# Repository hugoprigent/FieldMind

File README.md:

**Français** · [English](README.en.md)

# FieldMind

**Un rover de terrain dont les missions et la perception sont pilotées par une IA locale.**

<p align="center"><em>Le rover, sans coque, avec la remorque porte-drone et le drone posé dessus.</em></p>

Projet de Hugo Prigent, finaliste du **ASUS Ascent GX10 AI Developer Challenge 2026**.
FieldMind relie un rover Raspberry Pi / ESP32, un poste opérateur web et des modèles exécutés sur un ASUS Ascent GX10. La navigation, les vérifications des commandes et l'arrêt restent dans le logiciel du rover.

L'objectif : aider un opérateur à explorer et documenter une zone difficile d'accès, puis partager les observations entre robots. Le prototype vise un fonctionnement de terrain sans API d'IA externe ; cette autonomie de déploiement reste à valider.

[**Simulation publique du poste**](https://hugoprigent.com/fieldmind/) · [Page projet](https://hugoprigent.com/projets/fieldmind) · [Pitch de candidature](https://youtu.be/ZIIjRc_pI_E) · [Architecture](docs/architecture.md) · [État au 23 octobre](docs/status-2026-10-23.md) · [Validation](docs/validation.md)

> **État au 23 octobre 2026.**
> - Le rover roule, avec son châssis et son électronique visibles ; la coque n'est pas montée. Il tourne par le différentiel des roues arrière depuis la panne du servo de direction.
> - Navigation autonome testée en intérieur le 21 octobre avec le GX10 : exploration sur la consigne « explore la pièce » et trajet autonome aller-retour sur la carte lidar.
> - La remorque porte-drone est fabriquée ; ses volets sont commandés par servos (firmware ESP32-C5 ROVER_4). Le tractage autonome n'est pas validé.
> - Drone : flux vidéo reçu sur le Pi ; niveau de batterie pas encore lu de façon fiable ; le vol autonome n’est pas validé.
> - Huit modèles servis sur le GX10 : Qwen3.6-35B-A3B NVFP4, RoboBrain 2.5, D-FINE, Depth Anything V2, SAM 2.1, Qwen3-ASR, Qwen3-TTS, Qwen3-VL-Embedding.

*Vue CAO du rover avec sa coque et la remorque. Le rover réel roule pour l'instant sans la coque.*

## Le prototype

| | |
| :---: | :---: |
|  |  |
| Essai de navigation dans un couloir, avec les caméras stéréo et le lidar sur le châssis. | Câblage de la planche : Raspberry Pi, contrôleurs moteurs, convertisseurs, batterie. |
|  | |
| Carte capteurs I²C : IMU et écran OLED qui affiche l'état des capteurs. | |

## Le poste de pilotage

*Pilotage (simulation publique) : caméra gauche avec le couloir projeté devant le rover, vue 3D en incrustation, lidar et modes à droite.*

*Carte (essai réel du 21 octobre) : carte d'occupation lidar, trajet parcouru et chemin prévu en mode auto.*

*Vue 3D (essai réel du 21 octobre) : murs issus du lidar, objets nommés par la vision du GX10, caméra du rover en incrustation.*

## Essayer le logiciel actuel, sans matériel

Python **3.13+** et [uv](https://docs.astral.sh/uv/) :

```bash
git clone https://github.com/hugoprigent/FieldMind.git
cd FieldMind/software/rover
uv venv --python 3.13 .venv
uv pip install --python .venv/bin/python -r requirements-ci.txt
FIELDMIND_IA_PROFIL=aucun .venv/bin/python -m fieldmind \
  --materiel simulation --scenario jardin --hote 127.0.0.1
```

Ouvrir **http://127.0.0.1:8080/**. Le matériel est simulé ; navigation, missions, sécurité et interface sont le code du rover. Ce démarrage ne demande aucune clé d'API et ne commande aucun matériel réel.

La [simulation publique](https://hugoprigent.com/fieldmind/) sert ce même poste web : chaque navigateur reçoit son propre rover simulé, sans accès au matériel. Son serveur est [`software/rover/fieldmind/public_demo.py`](software/rover/fieldmind/public_demo.py) ; il se lance localement avec `.venv/bin/python -m fieldmind.public_demo --hote 127.0.0.1 --port 8085`. Son déploiement et ses clés ne sont pas dans ce dépôt. La [première démo MuJoCo](software/README.md) reste disponible.

## Comment ça fonctionne

```mermaid
flowchart LR
    O[Opérateur : carte, texte, voix] --> P[Poste web]
    P --> R[Raspberry Pi : missions, carte, navigation]
    R <--> G[GX10 : modèles locaux, images et outils]
    R --> S[Validation et superviseur de sécurité]
    L[Lidar, caméras, IMU, GNSS] --> R
    L --> S
    S --> E[ESP32-C5 : commandes, capteurs, watchdog]
    E --> M[Traction et direction]
```

- **Rover** : lidar C1, stéréo, odométrie, carte d'occupation, navigation et journal des essais.
- **IA et missions** : consignes écrites ou dites, exploration progressive, mémoire spatiale, confirmation d'un objet sur plusieurs images. Le GX10 choisit parmi des points calculés par le Pi ; le Pi revalide le choix, navigue et garde la sécurité. Le modèle ne commande pas directement les moteurs.
- **GX10** : agent et vision (Qwen3.6-35B-A3B NVFP4), pointage (RoboBrain 2.5), détection (D-FINE), profondeur (Depth Anything V2), segmentation (SAM 2.1), parole (Qwen3-ASR, Qwen3-TTS), empreintes d'images (Qwen3-VL-Embedding). Une analyse de scène a pris environ 6 à 9 s pendant les essais réels. [Configuration](software/rover/deploiement/gx10/README.md) et [état par rôle](software/rover/MODELES.md).
- **Électronique** : firmware XIAO ESP32-C5, chien de garde, écran OLED, capteurs I²C et liaison USB avec le Pi. La version ROVER_4 commande les deux servos des volets de la remorque.
- **Mécanique** : pneus TPU, châssis en bois, direction actuelle par différentiel des roues arrière ; remorque porte-drone imprimée et assemblée. La coque est dessinée mais pas montée ; un support de servo SG90 pour la direction est dessiné, pas validé sous charge.

Pendant la session ASUS, le GX10 était distant et joint par réseau privé. Les modèles tournent localement sur le GX10, mais un déploiement complet hors réseau, sur le terrain, n'est pas encore démontré.

## Explorer le dépôt

| Dossier | Contenu |
| --- | --- |
| [`software/rover/`](software/rover/README.md) | Logiciel actuel du Pi, simulateur du matériel, poste web et simulation publique isolée, tests, pont ROS 2 |
| [`software/esp32/esp_c5/`](software/esp32/esp_c5/README.md) | Firmware PlatformIO et programmes de banc |
| [`software/rover/deploiement/gx10/`](software/rover/deploiement/gx10/README.md) | Configuration des services IA et vérificateur d'API |
| [`software/`](software/README.md) | Première simulation MuJoCo (antérieure au rover actuel) |
| [`cao/`](cao/README.md) | Pièces STL courantes, scripts Fusion et plans de fabrication |
| [`hardware/`](hardware/README.md) | Connexions actuelles et études électroniques KiCad |
| [`docs/status-2026-10-23.md`](docs/status-2026-10-23.md) | État du rover, de la remorque, du drone et du GX10 au 23 octobre |
| [`docs/validation.md`](docs/validation.md) | Ce qui est mesuré, ce qui est simulé, ce qui reste à vérifier |

## Vérifier

Depuis `software/rover`, avec l'environnement créé ci-dessus :

```bash
.venv/bin/python -m pytest -q -m "not lent"
node --test tests/web/*.test.mjs
```

Les tests couvrent les contrôleurs, la sécurité, la navigation, les contrats IA et les scénarios simulés. Ils ne remplacent pas les essais physiques. [Détails et limites](docs/validation.md).

## Matériel et droits

Avant un essai réel, lire le [guide rover](software/rover/README.md) et les [connexions](hardware/electronics/CONNEXIONS.md), calibrer le montage et prévoir une coupure de traction. Les documents KiCad comportent des études antérieures à certains branchements actuels : leur statut est indiqué dans [hardware/README.md](hardware/README.md).

Cette édition sélectionne les sources utiles à la démonstration, sans les fichiers d'accès, secrets, journaux privés, rushes ni historique de travail. [Provenance](docs/publication.md).

Le code et les conceptions originaux sont présentés pour consultation ; aucune licence libre globale n'est accordée à ce stade. Les composants tiers conservent leurs licences. Voir [droits](RIGHTS.md) et [crédits](THIRD_PARTY_NOTICES.md).

## Langues et vidéos

Le poste et la page projet sont disponibles en français et en anglais : sélecteur **FR / EN** en haut à droite, détection de la langue du navigateur et choix mémorisé.

- [Présentation et essais en français](https://hugoprigent.com/media/fieldmind/presentation-20261023c.mp4)
- [Presentation and tests in English](https://hugoprigent.com/media/fieldmind/presentation-20261023-en.mp4)
- [Page projet en français](https://hugoprigent.com/projets/fieldmind?lang=fr) · [Project page in English](https://hugoprigent.com/projets/fieldmind?lang=en)

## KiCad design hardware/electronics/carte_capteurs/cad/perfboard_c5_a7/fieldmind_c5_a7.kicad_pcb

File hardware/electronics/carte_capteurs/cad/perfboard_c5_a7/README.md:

**Français** · [English](README.en.md)

# Projet courant A7 — une perfboard 4 × 6 cm, tous les fils dessous

Ouvrir `fieldmind_c5_a7.kicad_pro` dans KiCad 10. Toutes les sources ont été enregistrées par KiCad 10.0.6.

- **Schéma** : une feuille racine (XIAO, GNSS J4, extensions J6 et J8, Modulino Knob J7) et une sous-feuille, « Capteurs I2C et écran ».
- **PCB** :
  - **F.Cu** : uniquement les ponts de soudure du XIAO, côté écran ;
  - **B.Cu** : fils nus de la face dessous ;
  - **In1.Cu / In2.Cu** : fils isolés de la face dessous. Ce ne sont pas des couches réelles : elles séparent les fils qui se croisent pour le DRC ;
  - `PL1` porte les 280 trous ; `Cmts.User` porte les numéros de fils ;
  - la vue 3D s'ouvre avec Alt+3.
- Ne pas faire « Mettre à jour le PCB depuis le schéma » sans précaution : les pastilles de `PL1` portent leurs nets à la main.

Documentation : `../../perfboard_une_plaque_c5_a7.md`. Régénération : `scripts/generer_c5_a7.py --force`, ce qui **écrase toute édition manuelle**.

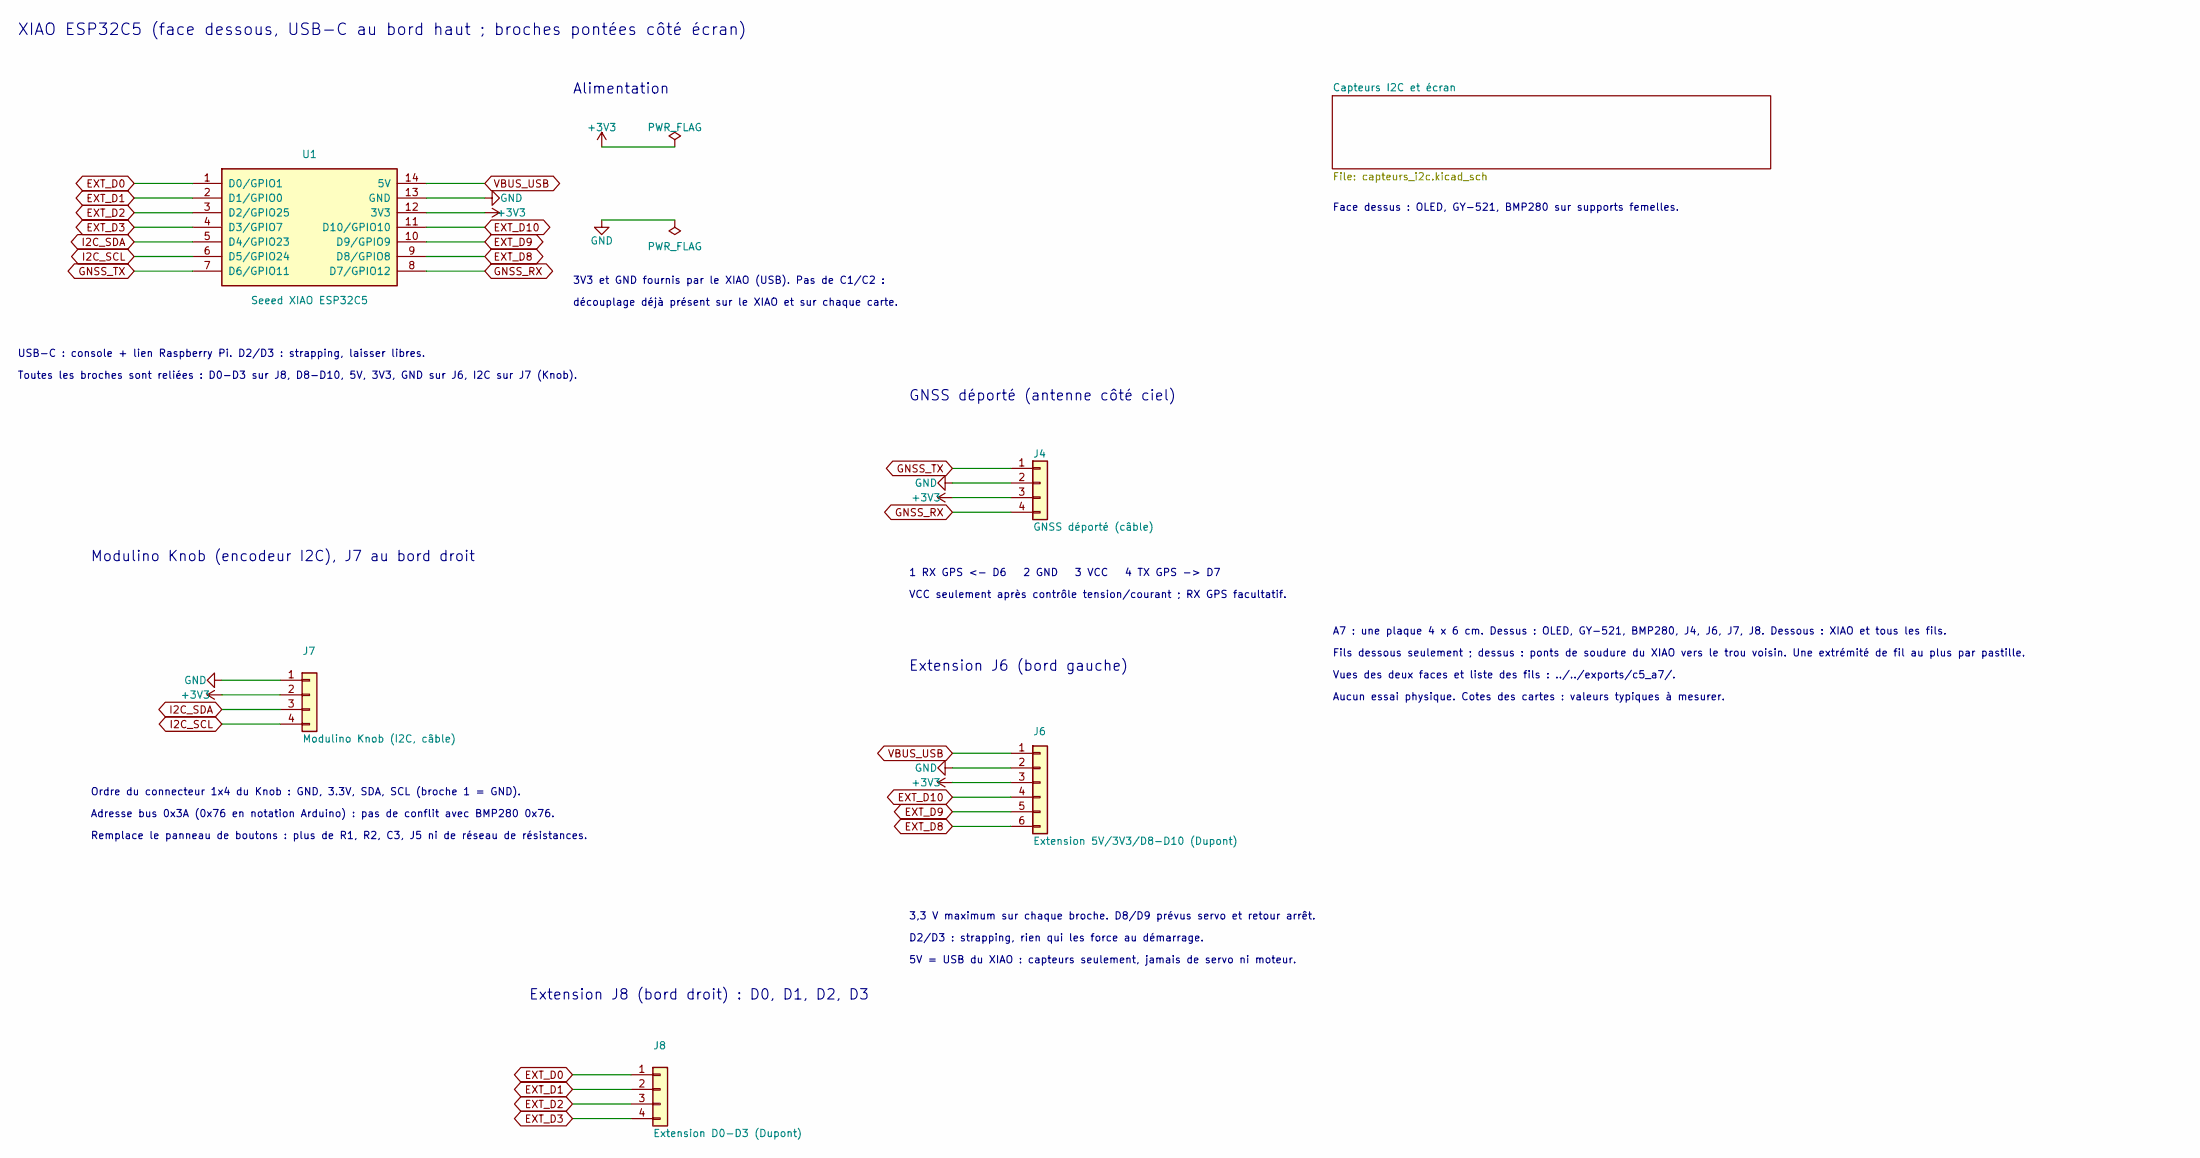
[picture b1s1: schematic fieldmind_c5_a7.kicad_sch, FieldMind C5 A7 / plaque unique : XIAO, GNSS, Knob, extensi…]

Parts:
J4: GNSS déporté (câble); A7_J4
J6: Extension 5V/3V3/D8-D10 (Dupont); A7_J6
J7: Modulino Knob (I2C, câble); A7_J7
J8: Extension D0-D3 (Dupont); A7_J8
U1: Seeed XIAO ESP32C5; A7_U1

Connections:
+3V3: J4.3 (VCC), J6.3 (3V3), J7.2 (3V3), U1.12 (3V3); also elsewhere on the board
EXT_D0: J8.1 (D0), U1.1 (D0); also elsewhere on the board
EXT_D1: J8.2 (D1), U1.2 (D1); also elsewhere on the board
EXT_D2: J8.3 (D2), U1.3 (D2); also elsewhere on the board
EXT_D3: J8.4 (D3), U1.4 (D3); also elsewhere on the board
EXT_D8: J6.6 (D8), U1.9 (D8); also elsewhere on the board
EXT_D9: J6.5 (D9), U1.10 (D9); also elsewhere on the board
EXT_D10: J6.4 (D10), U1.11 (D10); also elsewhere on the board
GND: J4.2 (GND), J6.2 (GND), J7.1 (GND), U1.13 (GND); also elsewhere on the board
GNSS_RX: J4.4 (TX_GPS), U1.8 (D7); also elsewhere on the board
GNSS_TX: J4.1 (RX_GPS), U1.7 (D6); also elsewhere on the board
I2C_SCL: J7.4 (SCL), U1.6 (D5); also elsewhere on the board
I2C_SDA: J7.3 (SDA), U1.5 (D4); also elsewhere on the board
VBUS_USB: J6.1 (5V), U1.14 (5V); also elsewhere on the board

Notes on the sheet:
Vues des deux faces et liste des fils : ../../exports/c5_a7/.
USB-C : console + lien Raspberry Pi. D2/D3 : strapping, laisser libres.
Aucun essai physique. Cotes des cartes : valeurs typiques à mesurer.
XIAO ESP32C5 (face dessous, USB-C au bord haut ; broches pontées côté écran)
VCC seulement après contrôle tension/courant ; RX GPS facultatif.
5V = USB du XIAO : capteurs seulement, jamais de servo ni moteur.
GNSS déporté (antenne côté ciel)
Extension J6 (bord gauche)
D2/D3 : strapping, rien qui les force au démarrage.
découplage déjà présent sur le XIAO et sur chaque carte.
Toutes les broches sont reliées : D0-D3 sur J8, D8-D10, 5V, 3V3, GND sur J6, I2C sur J7 (Knob).
Adresse bus 0x3A (0x76 en notation Arduino) : pas de conflit avec BMP280 0x76.
Alimentation
A7 : une plaque 4 x 6 cm. Dessus : OLED, GY-521, BMP280, J4, J6, J7, J8. Dessous : XIAO et tous les fils.
1 RX GPS <- D6 2 GND 3 VCC 4 TX GPS -> D7
3V3 et GND fournis par le XIAO (USB). Pas de C1/C2 :
Remplace le panneau de boutons : plus de R1, R2, C3, J5 ni de réseau de résistances.
Face dessus : OLED, GY-521, BMP280 sur supports femelles.
Fils dessous seulement ; dessus : ponts de soudure du XIAO vers le trou voisin. Une extrémité de fil au plus par pastille.
Modulino Knob (encodeur I2C), J7 au bord droit
Extension J8 (bord droit) : D0, D1, D2, D3
3,3 V maximum sur chaque broche. D8/D9 prévus servo et retour arrêt.
Ordre du connecteur 1x4 du Knob : GND, 3.3V, SDA, SCL (broche 1 = GND).

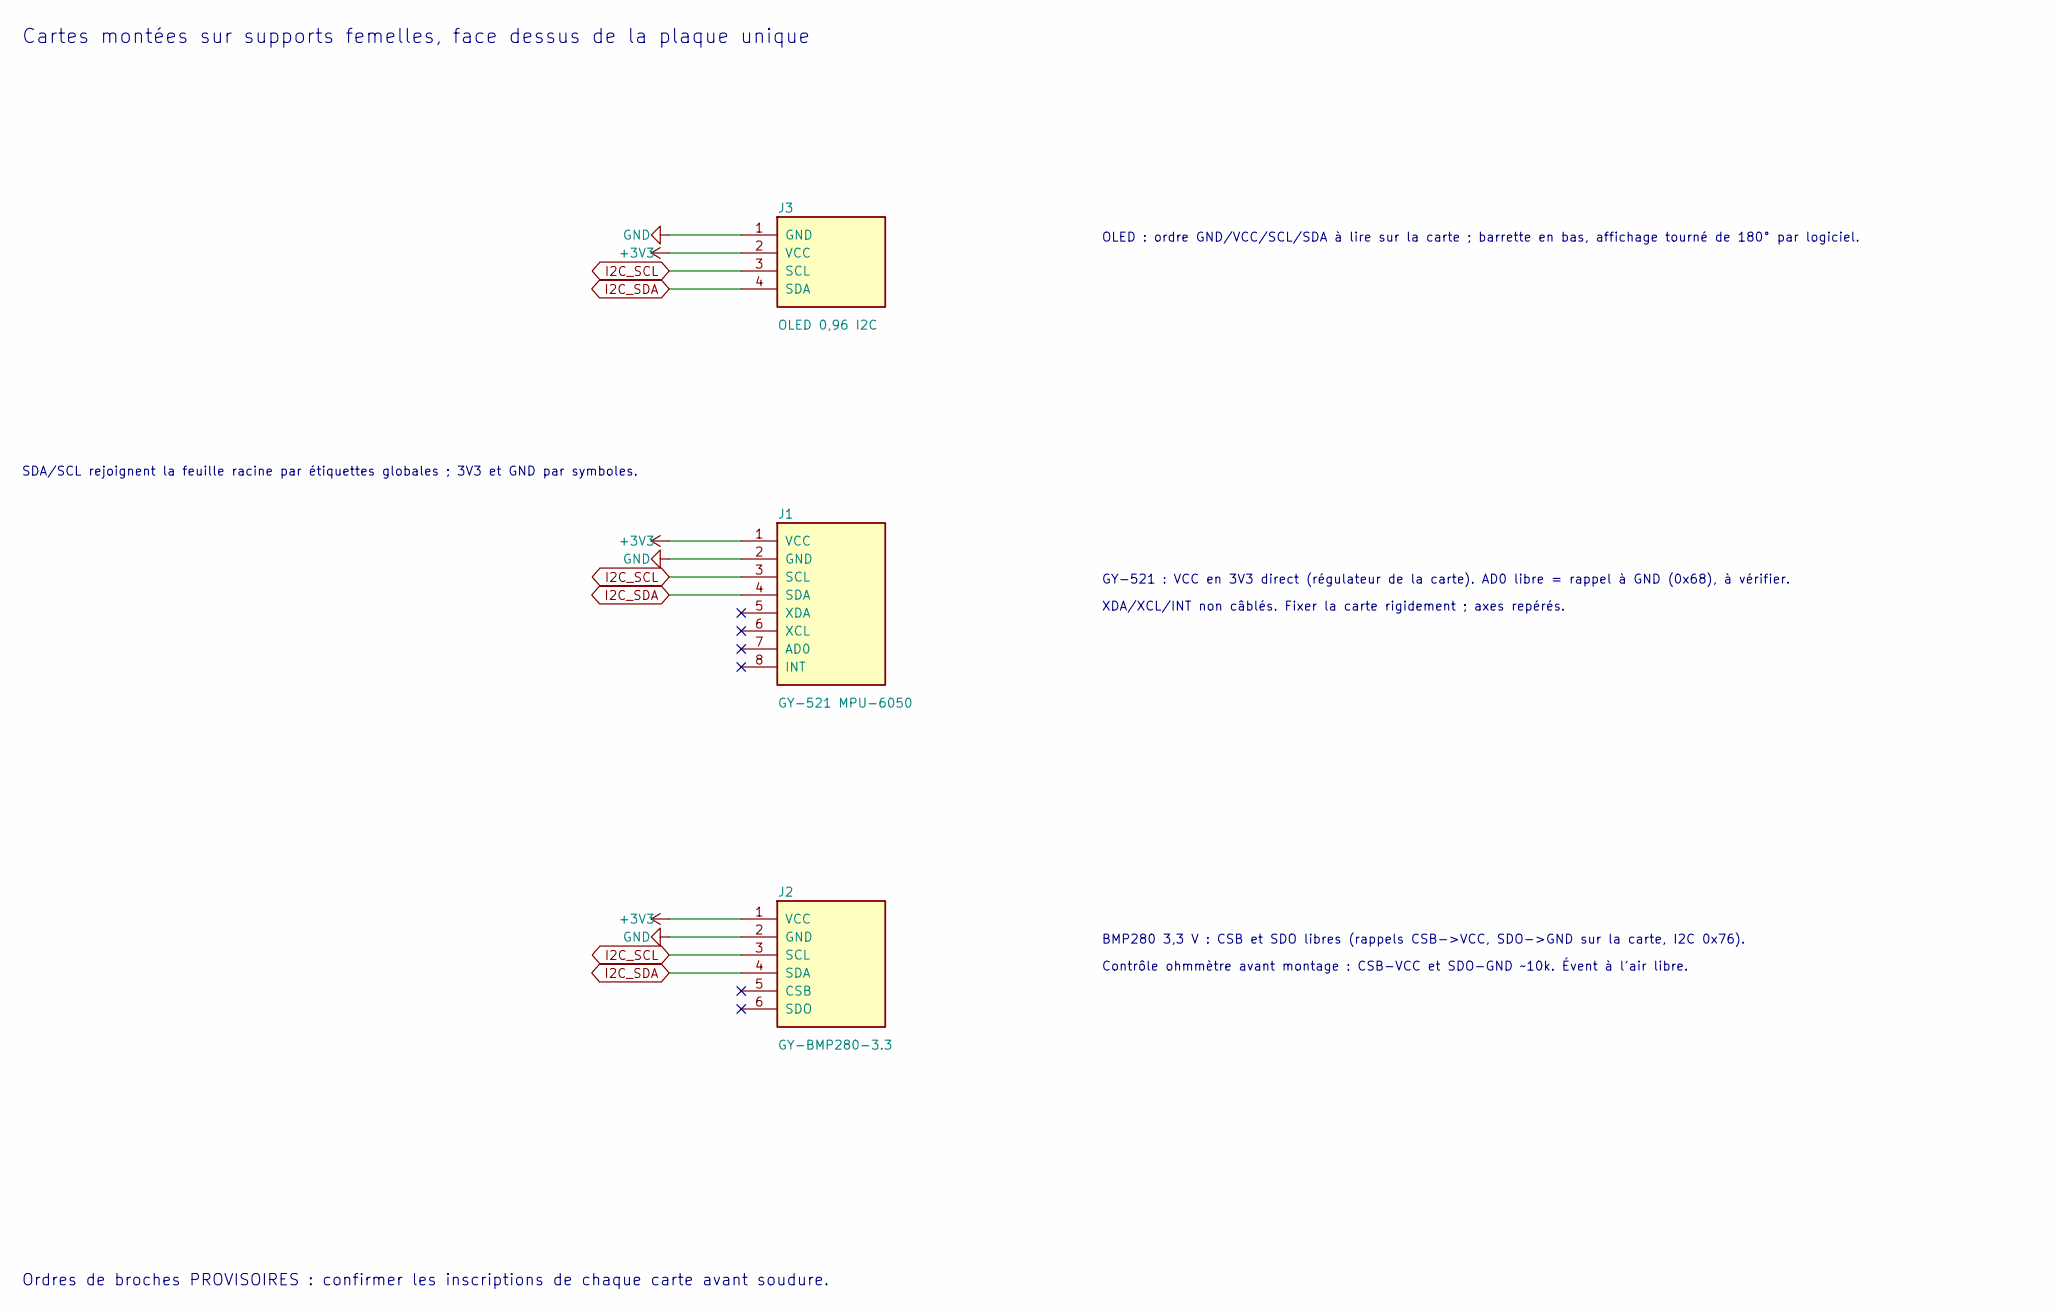
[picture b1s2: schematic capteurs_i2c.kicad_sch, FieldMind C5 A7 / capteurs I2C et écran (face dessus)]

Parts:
J1: GY-521 MPU-6050; A7_J1
J2: GY-BMP280-3.3; A7_J2
J3: OLED 0,96 I2C; A7_J3

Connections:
+3V3: J1.1 (VCC), J2.1 (VCC), J3.2 (VCC); also elsewhere on the board
GND: J1.2 (GND), J2.2 (GND), J3.1 (GND); also elsewhere on the board
I2C_SCL: J1.3 (SCL), J2.3 (SCL), J3.3 (SCL); also elsewhere on the board
I2C_SDA: J1.4 (SDA), J2.4 (SDA), J3.4 (SDA); also elsewhere on the board

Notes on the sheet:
Contrôle ohmmètre avant montage : CSB-VCC et SDO-GND ~10k. Évent à l’air libre.
BMP280 3,3 V : CSB et SDO libres (rappels CSB->VCC, SDO->GND sur la carte, I2C 0x76).
OLED : ordre GND/VCC/SCL/SDA à lire sur la carte ; barrette en bas, affichage tourné de 180° par logiciel.
SDA/SCL rejoignent la feuille racine par étiquettes globales ; 3V3 et GND par symboles.
Cartes montées sur supports femelles, face dessus de la plaque unique
Ordres de broches PROVISOIRES : confirmer les inscriptions de chaque carte avant soudure.
XDA/XCL/INT non câblés. Fixer la carte rigidement ; axes repérés.
GY-521 : VCC en 3V3 direct (régulateur de la carte). AD0 libre = rappel à GND (0x68), à vérifier.

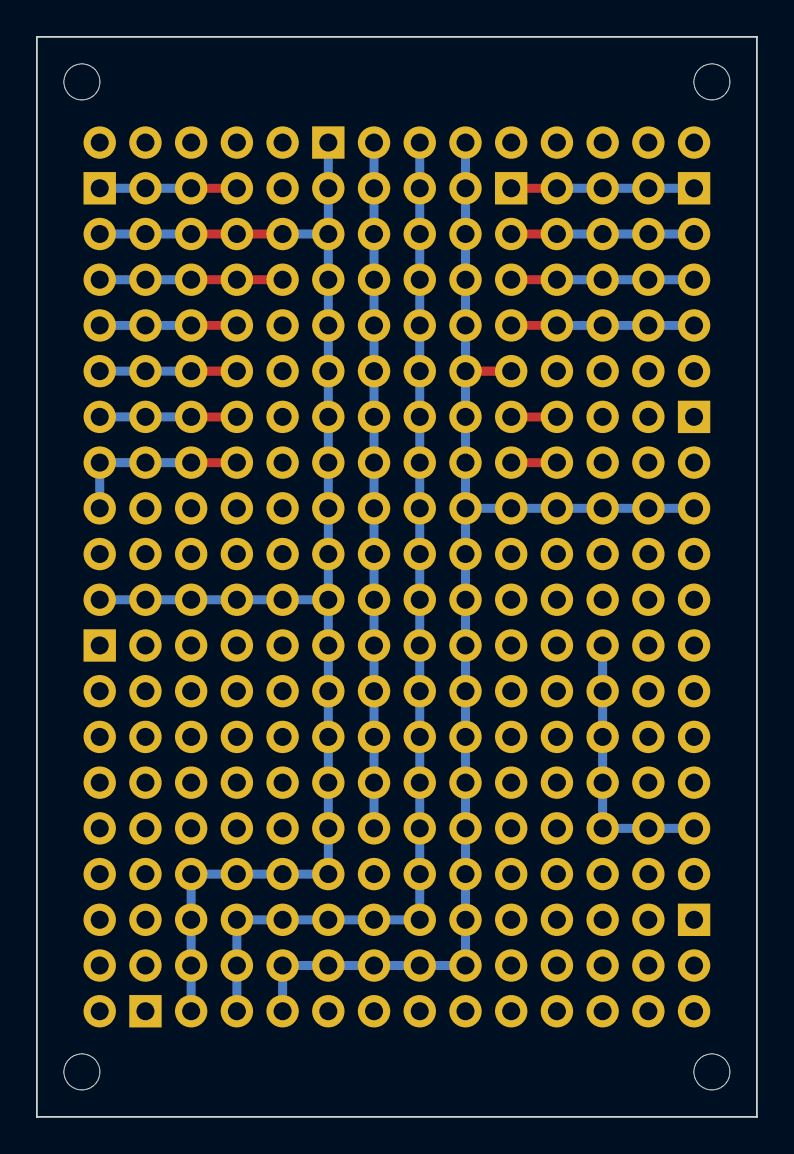
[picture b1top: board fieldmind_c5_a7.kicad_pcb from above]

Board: 4 copper layers, 40.0 x 60.0 mm, 9 parts (1 on the bottom side), 14 nets.

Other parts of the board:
PL1: Perfboard 4x6 cm 14x20 trous, double face; A7_PERF

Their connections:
+3V3: PL1.B4, PL1.B16, PL1.B17, PL1.B18, PL1.B19, PL1.C4, PL1.C16, PL1.D16, PL1.E4, PL1.E16, PL1.G2, PL1.G3, PL1.G4, PL1.G5, PL1.G6, PL1.G7, PL1.G8, PL1.G9, PL1.G10, PL1.G11, PL1.G12, PL1.G13, PL1.G14, PL1.G15, PL1.G16, PL1.J1, PL1.J18, PL1.J19, PL1.J20, PL1.K1, PL1.K18, PL1.L1, PL1.L18, PL1.M1, PL1.M18, PL1.N1; also elsewhere on the board
EXT_D0: PL1.K2, PL1.L2, PL1.M2; also elsewhere on the board
EXT_D1: PL1.K3, PL1.L3, PL1.M3; also elsewhere on the board
EXT_D2: PL1.K4, PL1.L4, PL1.M4; also elsewhere on the board
EXT_D3: PL1.K5, PL1.L5, PL1.M5; also elsewhere on the board
EXT_D8: PL1.B7, PL1.C7; also elsewhere on the board
EXT_D9: PL1.B6, PL1.C6; also elsewhere on the board
EXT_D10: PL1.B5, PL1.C5; also elsewhere on the board
GND: PL1.B3, PL1.B11, PL1.C3, PL1.C11, PL1.C17, PL1.C18, PL1.C19, PL1.D11, PL1.D17, PL1.E3, PL1.E11, PL1.E17, PL1.F2, PL1.F3, PL1.F4, PL1.F5, PL1.F6, PL1.F7, PL1.F8, PL1.F9, PL1.F10, PL1.F11, PL1.F12, PL1.F13, PL1.F14, PL1.F15, PL1.F16, PL1.F17, PL1.J17, PL1.K17, PL1.L17, PL1.M17; also elsewhere on the board
GNSS_RX: PL1.A8, PL1.B8, PL1.C8; also elsewhere on the board
GNSS_TX: PL1.B12, PL1.C12, PL1.D12, PL1.E12, PL1.K8, PL1.L8; also elsewhere on the board
I2C_SCL: PL1.D18, PL1.D19, PL1.E18, PL1.F18, PL1.G18, PL1.H2, PL1.H3, PL1.H4, PL1.H5, PL1.H6, PL1.H7, PL1.H8, PL1.H9, PL1.H10, PL1.H11, PL1.H12, PL1.H13, PL1.H14, PL1.H15, PL1.H16, PL1.H17, PL1.H18, PL1.J12, PL1.K7, PL1.K12, PL1.L12, PL1.L13, PL1.L14, PL1.L15, PL1.L16, PL1.M12, PL1.M16, PL1.N11, PL1.N12; also elsewhere on the board
I2C_SDA: PL1.E19, PL1.F19, PL1.G19, PL1.H19, PL1.I2, PL1.I3, PL1.I4, PL1.I5, PL1.I6, PL1.I7, PL1.I8, PL1.I9, PL1.I10, PL1.I11, PL1.I12, PL1.I13, PL1.I14, PL1.I15, PL1.I16, PL1.I17, PL1.I18, PL1.I19, PL1.J9, PL1.J16, PL1.K9, PL1.K16, PL1.L9, PL1.M9; also elsewhere on the board
VBUS_USB: PL1.B2, PL1.C2; also elsewhere on the board
